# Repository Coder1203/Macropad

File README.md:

# CadPad (Hack Club Hackpad)

This was my first hardware project and also the first time for me to use a CAD software (it ragebaited me so hard, so I named my project CadPad :D). It has 9 keys, 1 rotary encoder and 1 OLED screen and a very simple case. I mostly followed the guide for the beginning part but then had to read up on a lot of stuff to complete this project.

## BOM

| Item | Quantity |
| --- | --- |
| pcb | 1x |
| Seeed XIAO RP2040 | 1x |
| OLED Display 0.91 inch | 1x |
| EC11 rotary encoder | 1x |
| Cherry MX Switches | 9x |
| Blank DSA keycaps | 9x |
| Through-hole 1N4148 Diodes | 9x |
| M3×16 mm Screws | 4x |

All of the parts are already present in the kit mentioned at Hackpad page, so no extra costs i think?

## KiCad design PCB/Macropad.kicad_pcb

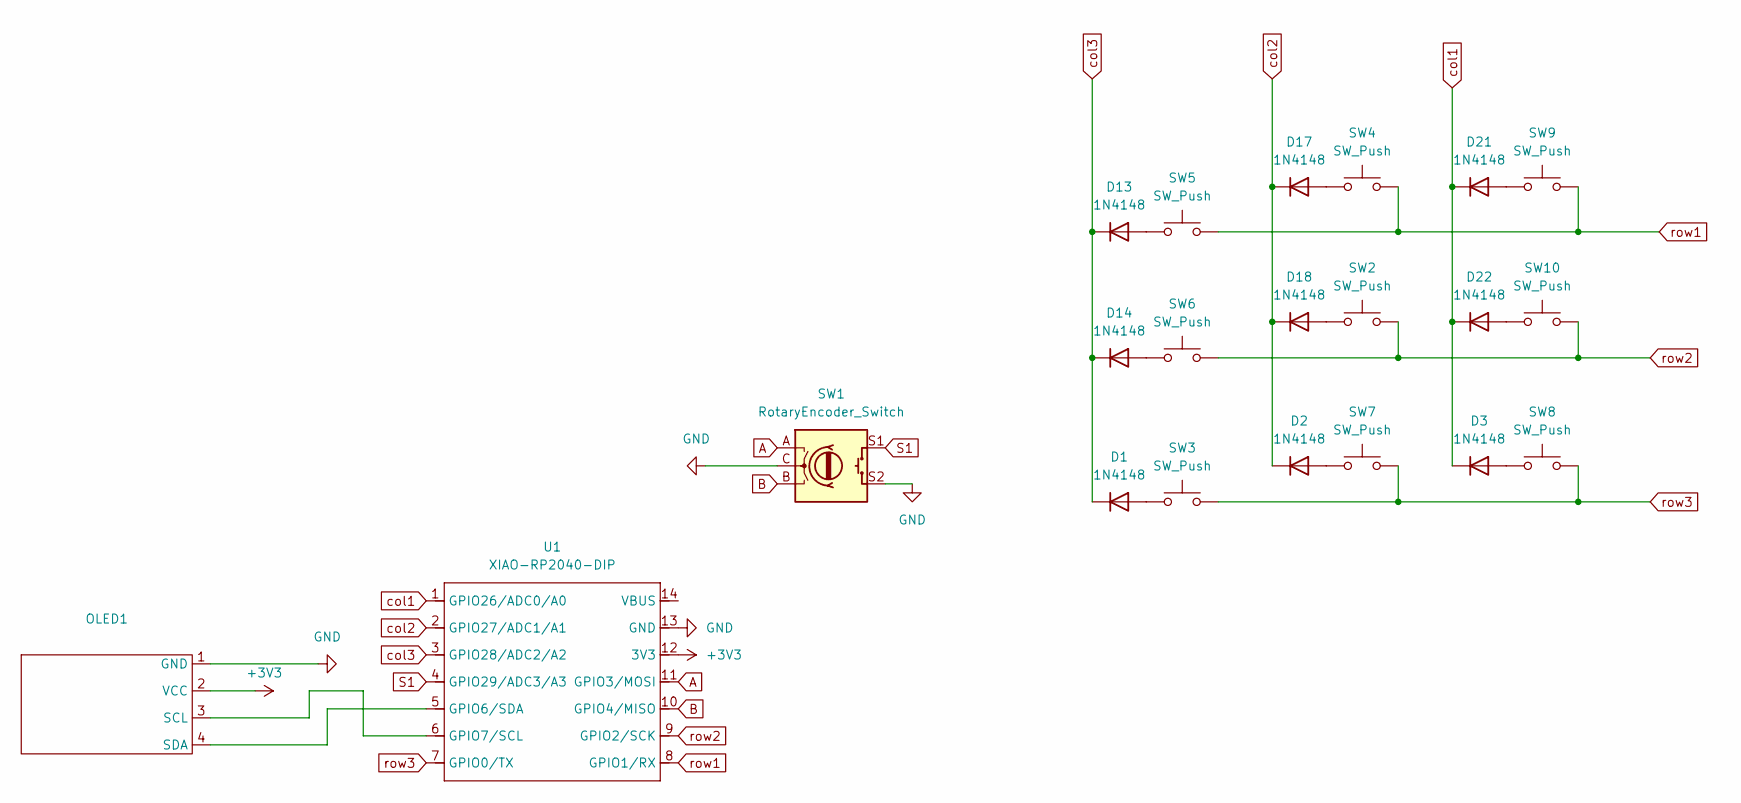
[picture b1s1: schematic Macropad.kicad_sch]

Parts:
D1, D2, D3, D13, D14, D17, D18, D21, D22: 1N4148; D_DO-35_SOD27_P7.62mm_Horizontal
OLED1: (no value)
SW1: RotaryEncoder_Switch; RotaryEncoder_Alps_EC11E-Switch_Vertical_H20mm
SW2, SW3, SW4, SW5, SW6, SW7, SW8, SW9, SW10: SW_Push; SW_Cherry_MX_1.00u_PCB
U1: XIAO-RP2040-DIP; XIAO-SAMD21-DIP

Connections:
+3V3: OLED1.2 (VCC), U1.12 (3V3)
A: SW1.A, U1.11 (GPIO3/MOSI)
B: SW1.B, U1.10 (GPIO4/MISO)
GND: OLED1.1 (GND), SW1.C, SW1.S2, U1.13 (GND)
unnamed: D1.2 (A), SW3.1
unnamed: D2.2 (A), SW7.1
unnamed: D3.2 (A), SW8.1
unnamed: D13.2 (A), SW5.1
unnamed: D14.2 (A), SW6.1
unnamed: D17.2 (A), SW4.1
unnamed: D18.2 (A), SW2.1
unnamed: D21.2 (A), SW9.1
unnamed: D22.2 (A), SW10.1
unnamed: OLED1.3 (SCL), U1.6 (GPIO7/SCL)
unnamed: OLED1.4 (SDA), U1.5 (GPIO6/SDA)
S1: SW1.S1, U1.4 (GPIO29/ADC3/A3)
col1: D3.1 (K), D21.1 (K), D22.1 (K), U1.1 (GPIO26/ADC0/A0)
col2: D2.1 (K), D17.1 (K), D18.1 (K), U1.2 (GPIO27/ADC1/A1)
col3: D1.1 (K), D13.1 (K), D14.1 (K), U1.3 (GPIO28/ADC2/A2)
row1: SW4.2, SW5.2, SW9.2, U1.8 (GPIO1/RX)
row2: SW2.2, SW6.2, SW10.2, U1.9 (GPIO2/SCK)
row3: SW3.2, SW7.2, SW8.2, U1.7 (GPIO0/TX)

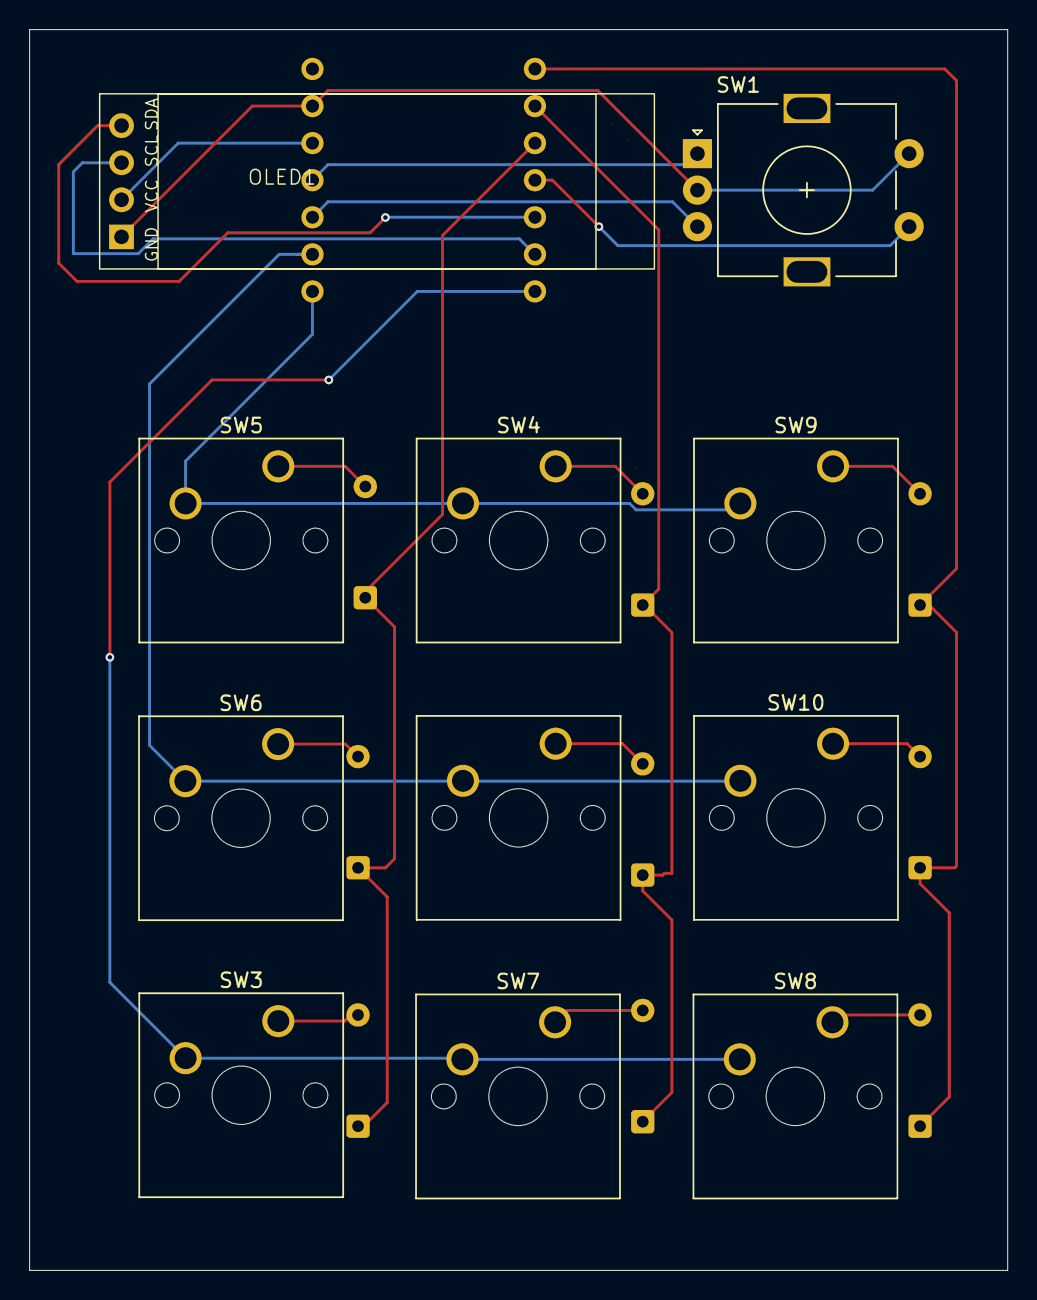
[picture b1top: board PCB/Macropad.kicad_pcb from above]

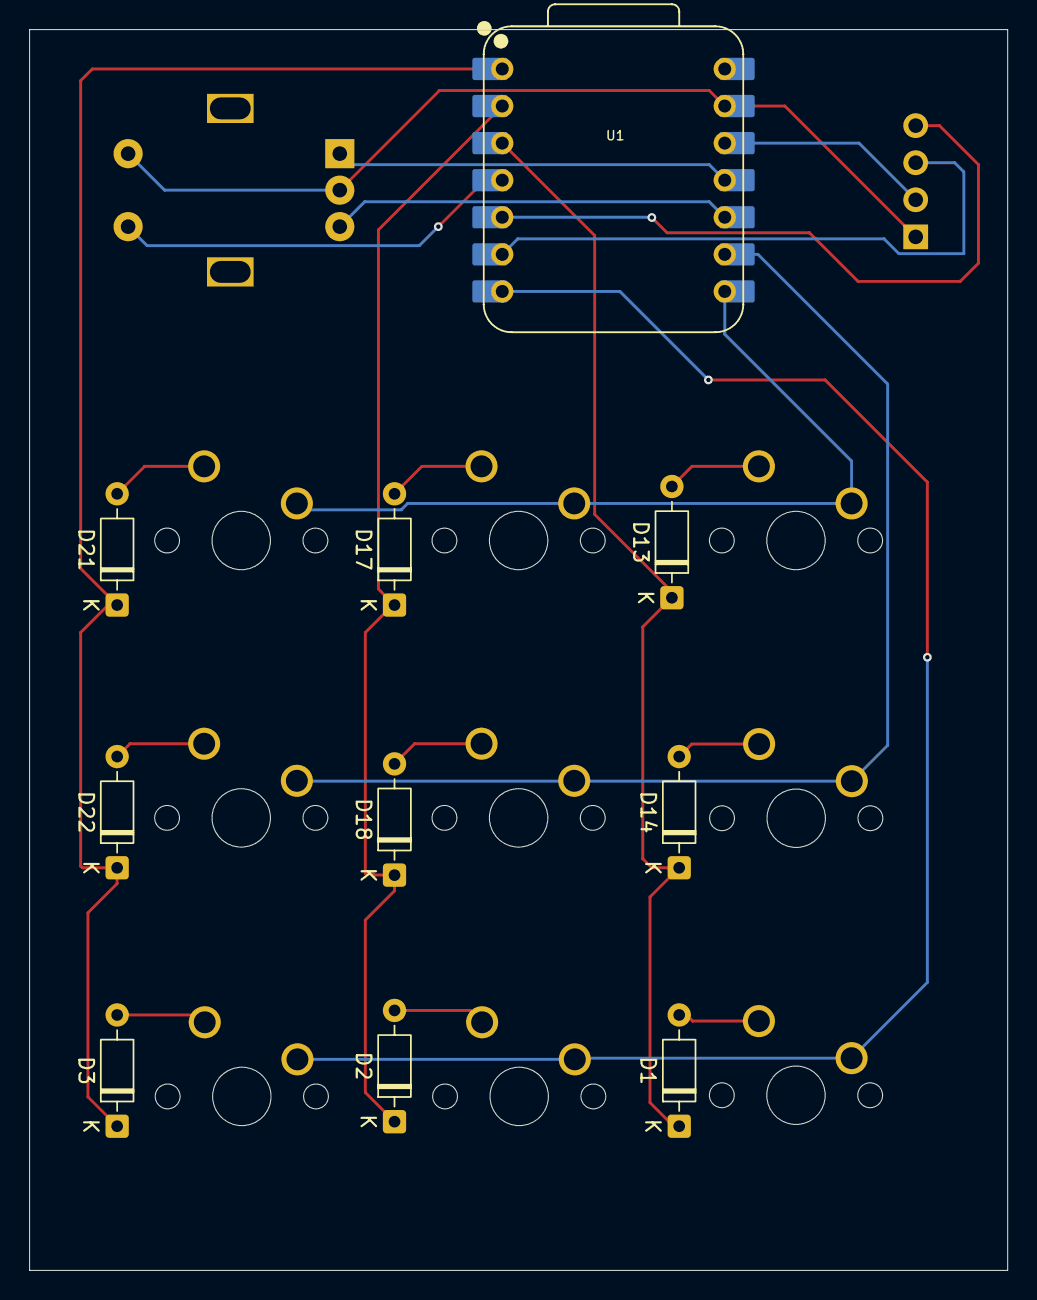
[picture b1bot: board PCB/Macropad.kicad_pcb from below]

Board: 2 copper layers, 67.0 x 85.0 mm, 21 parts (10 on the bottom side), 22 nets.

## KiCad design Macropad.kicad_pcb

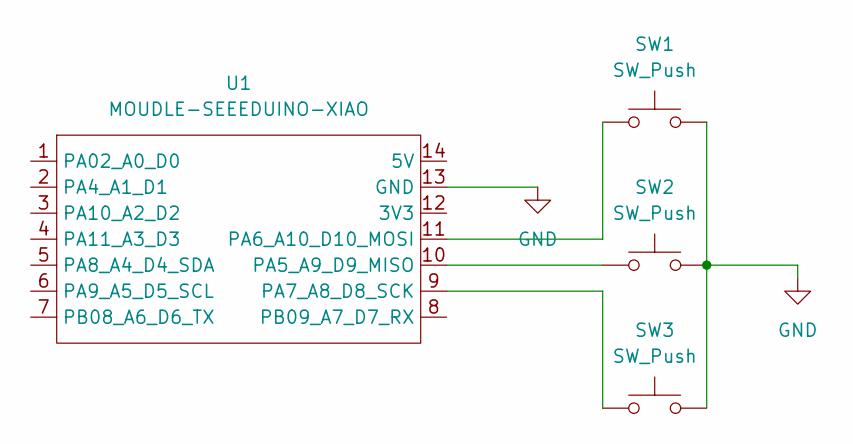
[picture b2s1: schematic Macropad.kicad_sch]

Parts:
SW1, SW2, SW3: SW_Push; SW_Cherry_MX_1.00u_PCB
U1: MOUDLE-SEEEDUINO-XIAO; XIAO-Generic-Hybrid-14P-2.54-21X17.8MM

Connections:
GND: SW1.2, SW2.2, SW3.2, U1.13 (GND)
unnamed: SW2.1, U1.10 (PA5_A9_D9_MISO)
unnamed: SW1.1, U1.11 (PA6_A10_D10_MOSI)
unnamed: SW3.1, U1.9 (PA7_A8_D8_SCK)

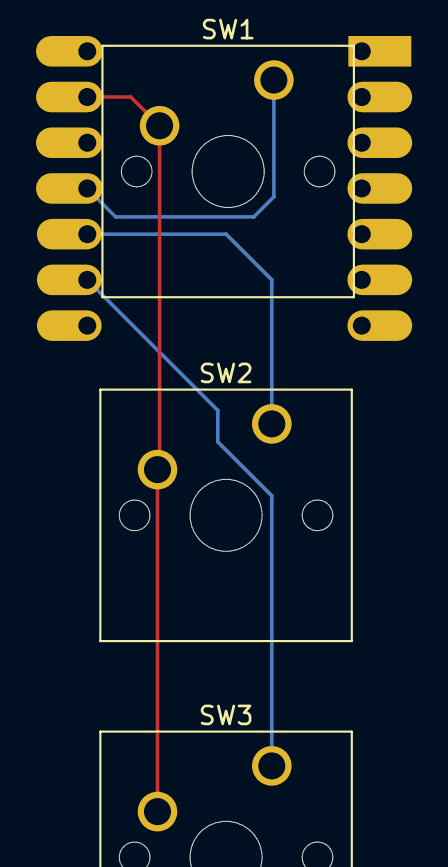
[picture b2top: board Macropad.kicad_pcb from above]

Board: 2 copper layers, 4 parts (1 on the bottom side), 4 nets.

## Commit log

2026-03-27 v1.0
2026-03-27 images
2026-03-27 updated some stuff
2026-03-29 Updated PCB
2026-03-29 v1.1
